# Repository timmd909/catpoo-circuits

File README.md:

This is a now defunct repo of various circuits that I made
while learning how to use KiCad.

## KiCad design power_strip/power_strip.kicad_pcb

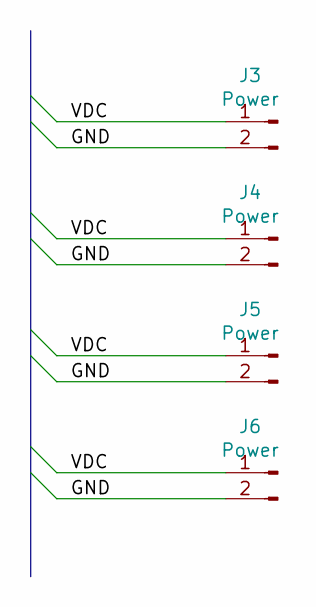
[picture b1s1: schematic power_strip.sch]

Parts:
J3, J4, J5, J6: Power; TerminalBlock_Pololu-2_P5.00mm

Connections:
/GND: J3.2, J4.2, J5.2, J6.2
/VDC: J3.1, J4.1, J5.1, J6.1

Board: 2 copper layers, 4 parts (0 on the bottom side), 2 nets, no tracks yet.

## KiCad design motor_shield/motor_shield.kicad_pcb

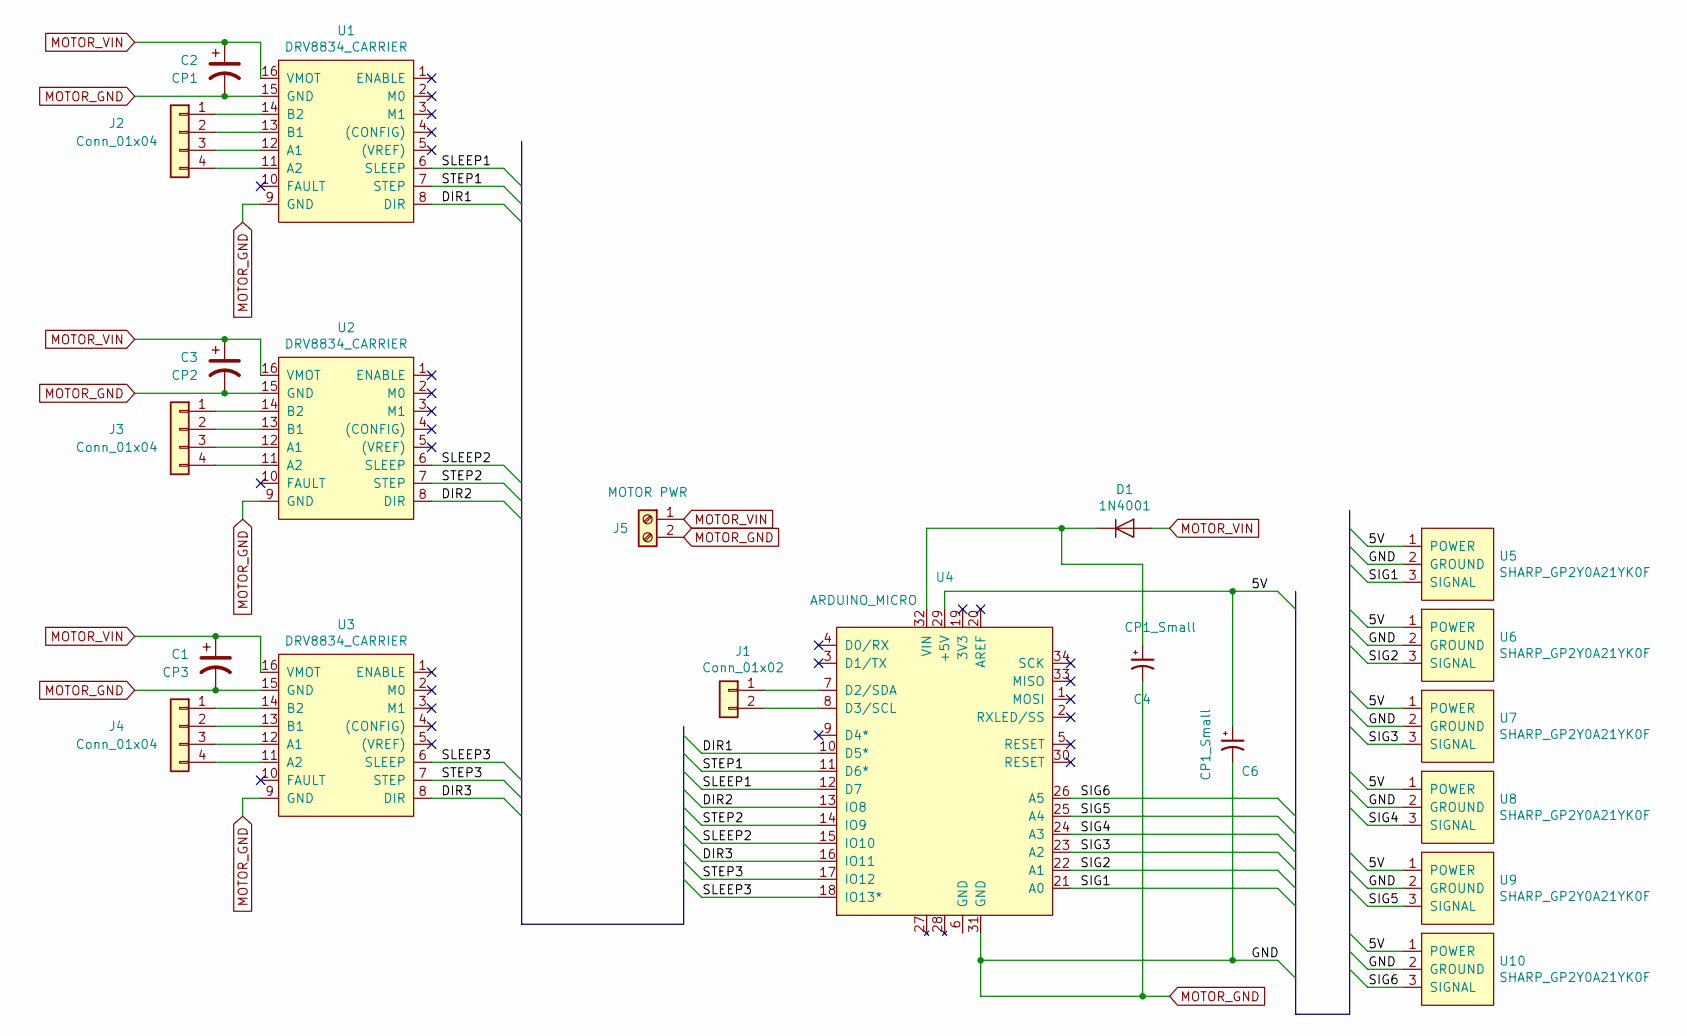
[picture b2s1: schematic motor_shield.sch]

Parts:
C1: CP3; CP_Radial_D8.0mm_P3.50mm
C2: CP1; CP_Radial_D8.0mm_P3.50mm
C3: CP2; CP_Radial_D8.0mm_P3.50mm
C4, C6: CP1_Small; CP_Radial_D5.0mm_P2.50mm
D1: 1N4001; D_DO-41_SOD81_P10.16mm_Horizontal
J1: Conn_01x02; JST_XH_B02B-XH-A_1x02_P2.50mm_Vertical
J2, J3, J4: Conn_01x04; JST_XH_B04B-XH-A_1x04_P2.50mm_Vertical
J5: MOTOR PWR; TerminalBlock_Pololu-2_P5.00mm
U1, U2, U3: DRV8834_CARRIER; DRV8834
U4: ARDUINO_MICRO
U5, U6, U7, U8, U9, U10: SHARP_GP2Y0A21YK0F; JST_XH_B03B-XH-A_1x03_P2.50mm_Vertical

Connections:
/5V: C6.1, U4.29 (+5V), U5.1 (POWER), U6.1 (POWER), U7.1 (POWER), U8.1 (POWER), U9.1 (POWER), U10.1 (POWER)
/DIR1: U1.8 (DIR), U4.10 (D5*)
/DIR2: U2.8 (DIR), U4.13 (IO8)
/DIR3: U3.8 (DIR), U4.16 (IO11)
/SIG1: U4.21 (A0), U5.3 (SIGNAL)
/SIG2: U4.22 (A1), U6.3 (SIGNAL)
/SIG3: U4.23 (A2), U7.3 (SIGNAL)
/SIG4: U4.24 (A3), U8.3 (SIGNAL)
/SIG5: U4.25 (A4), U9.3 (SIGNAL)
/SIG6: U4.26 (A5), U10.3 (SIGNAL)
/SLEEP1: U1.6 (SLEEP), U4.12 (D7)
/SLEEP2: U2.6 (SLEEP), U4.15 (IO10)
/SLEEP3: U3.6 (SLEEP), U4.18 (IO13*)
/STEP1: U1.7 (STEP), U4.11 (D6*)
/STEP2: U2.7 (STEP), U4.14 (IO9)
/STEP3: U3.7 (STEP), U4.17 (IO12)
MOTOR_GND: C1.2, C2.2, C3.2, C4.2, C6.2, J5.2, U1.9 (GND), U1.15 (GND), U2.9 (GND), U2.15 (GND), U3.9 (GND), U3.15 (GND), U4.31 (GND), U5.2 (GROUND), U6.2 (GROUND), U7.2 (GROUND), U8.2 (GROUND), U9.2 (GROUND), U10.2 (GROUND)
MOTOR_VIN: C1.1, C2.1, C3.1, D1.2 (A), J5.1, U1.16 (VMOT), U2.16 (VMOT), U3.16 (VMOT)
unnamed: C4.1, D1.1 (K), U4.32 (VIN)
unnamed: J1.1, U4.7 (D2/SDA)
unnamed: J1.2, U4.8 (D3/SCL)
unnamed: J2.1, U1.14 (B2)
unnamed: J2.2, U1.13 (B1)
unnamed: J2.3, U1.12 (A1)
unnamed: J2.4, U1.11 (A2)
unnamed: J3.1, U2.14 (B2)
unnamed: J3.2, U2.13 (B1)
unnamed: J3.3, U2.12 (A1)
unnamed: J3.4, U2.11 (A2)
unnamed: J4.1, U3.14 (B2)
unnamed: J4.2, U3.13 (B1)
unnamed: J4.3, U3.12 (A1)
unnamed: J4.4, U3.11 (A2)

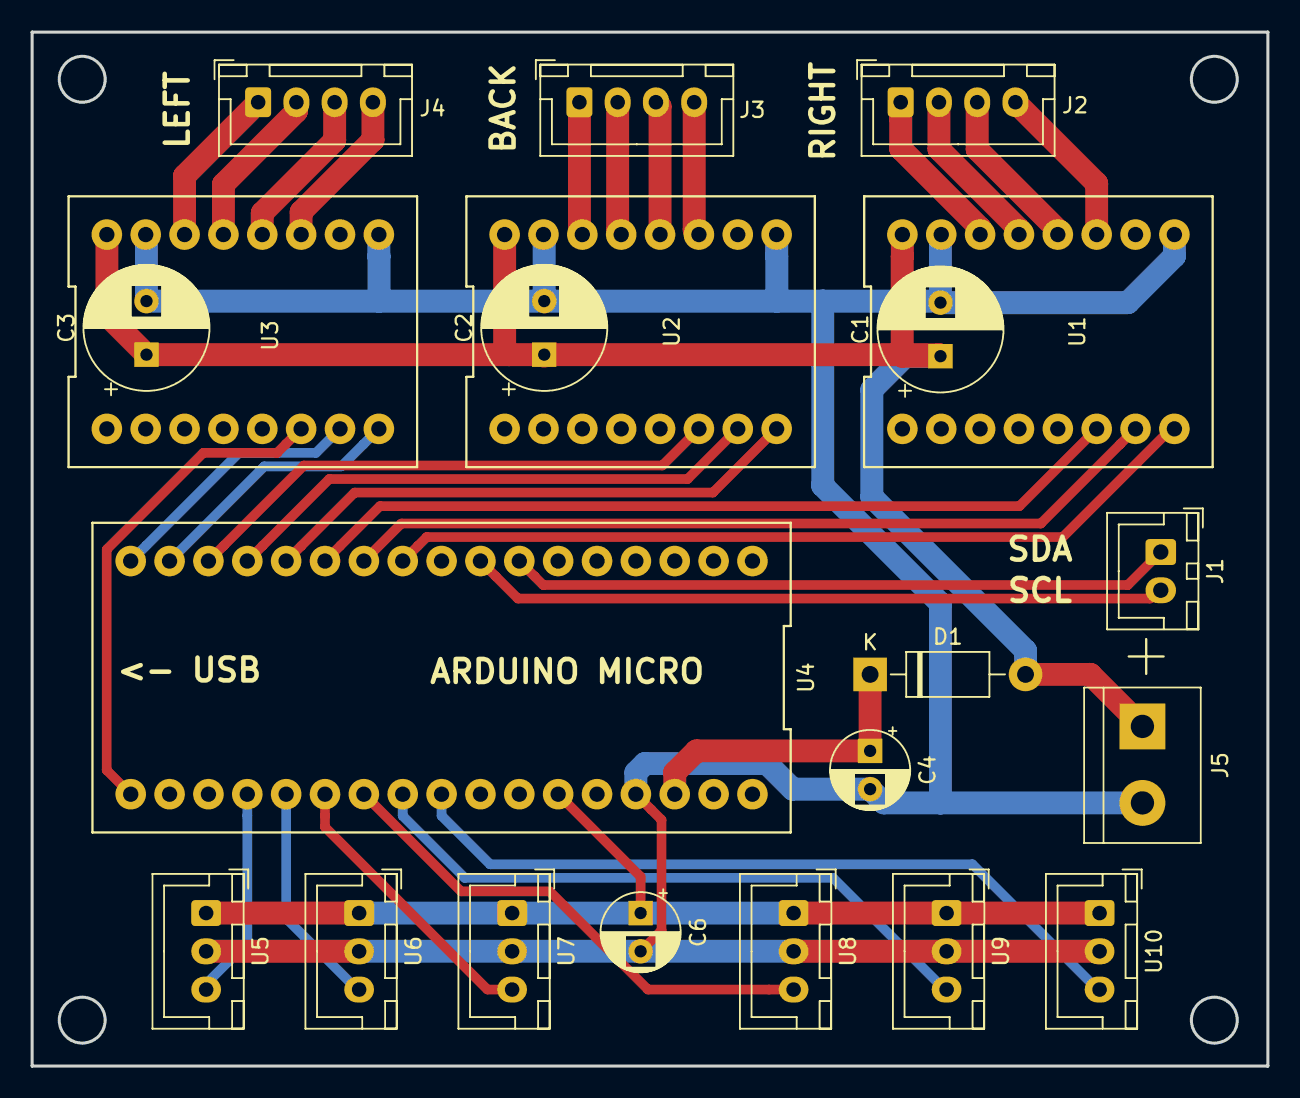
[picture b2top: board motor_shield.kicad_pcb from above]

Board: 2 copper layers, 80.8 x 67.6 mm, 21 parts (0 on the bottom side), 33 nets.

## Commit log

2018-05-22 Add arduino shield submodule
2018-05-22 Add brainstem schematic
2018-05-22 add kicad symbol library
2018-05-22 Messing around w/ kicad
2018-05-22 Messing around
2018-05-22 Before auto-routing
2018-05-22 Fritzing is the best for easy stuff
    Anything that is more complicated, will not work out well...
    but for what I need, this will work good enough.
2018-05-22 more tweaks
2018-05-22 Add motherboard circuit
2018-05-22 Motherboard almost finished
2018-05-23 Done playing around w/ this tonight
2018-05-23 And it's done. Order has been placed
    My first PCB!
2018-05-23 Added convenient spots for enabling/disabling parts of the board
    Time to reorder at https://oshpark.com/
    OMG are they awesome at ordering
2018-06-19 Move old files out of the way
    Gonna do as clean as possible in Fritzing.
    KiCad is a little beyond the beginners. I've been learning and
    experimenting for almost a year now. Time to actually
    just get shit done.
    I'll do the mini-bot series in KiCad to make Jerry happy
    in fall...
2018-06-19 Add externals used as reference/models in this project
    For storing files after downloading 3rd party assets.
2018-07-05 Add new simple smaller boards
2018-07-06 Widen the power holes, minor tweaks, added logos
2018-08-15 Remove old sketchs and such
2019-01-04 Add WIP new Arduino design w/ JST connectors
2019-01-05 Remove old Fritzing files
    Moving them out of the way so I'm less tempted to be lazy
    and not learn KiCad
2019-01-06 Schematic part done, moving on to PCB
2019-01-26 WIP: v5....
    This just isn't working... gonna have to go full kicad
2019-01-26 Adding mobo v4 output before switching back to kicad
2019-02-13 Clean out everything
2019-02-13 Add new design project
2019-02-13 Add new CATPOO symbol library
2019-02-18 Add proxy sensor
2019-02-18 Continued work on new schematic
2019-02-21 Removed buses, wired everything up more simple like
    Seemed easier for me to visual the connections w/o the bus lines
2019-02-22 Add new footprint library
2019-02-22 Assigned footprints, ERC clean up
2019-03-01 WIP board layout
2019-03-01 Remove existing submodules
2019-03-14 Add new RPI and kicad libraries
2019-03-14 Continued work on motor shield
2019-03-21 Fix mobo schematic
    flipped the order of dir, step, sleep to make it easier to route wires
2019-03-22 Finish circuit board design
    off to oshpark!
2019-03-22 Updated origin but no functional changes
2019-03-28 Remove the RPI connector and power supply
    The board for holding the Arduino was too complicated, and
    didn't allow me to use the protoshield on the RPI. This
    also is 33% less expensive to fabricate.
2019-03-30 Add power strip base
2019-03-30 Update power strip. Circuit done
2019-04-07 Finish power strip
    It now only does exactly what it needs to do, and that's
    split an incoming power into 3 other outputs.
2021-07-29 Add defunct warning
